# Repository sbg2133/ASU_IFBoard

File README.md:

# ASU_IFBoard
IF board schematics and PCB

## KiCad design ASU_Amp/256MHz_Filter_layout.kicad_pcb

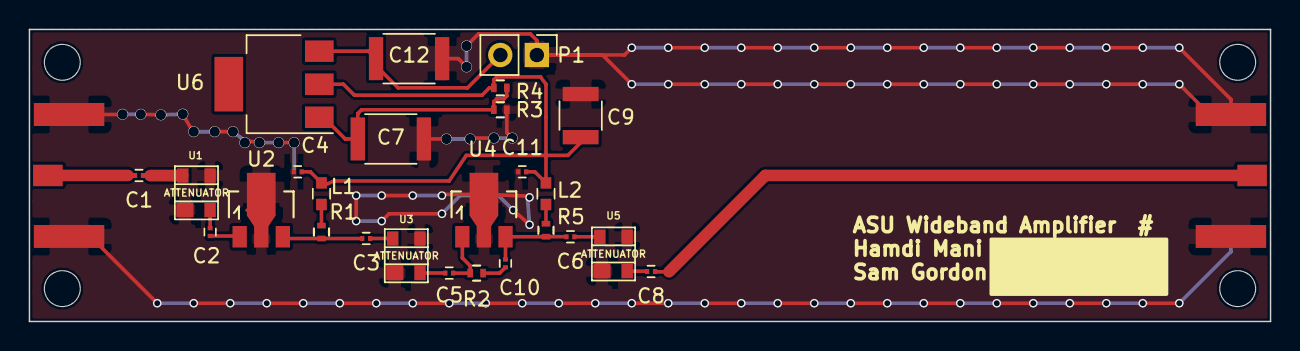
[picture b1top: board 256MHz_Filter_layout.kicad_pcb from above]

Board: 2 copper layers, 86.4 x 20.3 mm, 26 parts (0 on the bottom side), 17 nets.

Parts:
C1, C2, C3, C5, C6, C8, C10: 100pF; C_0201
C4, C11: 20pF; C_0201
C7, C12: 10uF; C_1812
C9: 100uF; C_1210
L1, L2: 1000nH; C_0603
P1: CONN_01X02; Pin_Header_Straight_1x02_Pitch2.54mm
R1, R2, R3, R4, R5: R; R_0402
U1, U3, U5: ATTENUATOR; sot143B
U2, U4: AMP; SOT89-3_Housing
U6: LM117; SOT-223

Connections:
/Vbias: C4.2, C9.2, C11.2, L1.2, L2.2, R3.1, U6.2
GND: C4.1, C7.1, C9.1, C11.1, C12.1, P1.1, R4.2, U1.1, U1.3, U2.2, U3.1, U3.3, U4.2, U5.1, U5.3
unnamed: C1.1, U1.4
unnamed: C2.1, U2.1
unnamed: C2.2, U1.2
unnamed: C3.1, U3.4
unnamed: C3.2, R1.2, U2.3
unnamed: C5.1, R2.2, U4.1
unnamed: C5.2, U3.2
unnamed: C6.1, U5.4
unnamed: C7.2, R3.2, R4.1, U6.1
unnamed: C8.2, U5.2
unnamed: C6.2, C10.1, R5.2, U4.3
unnamed: C10.2, R2.1
unnamed: C12.2, P1.2, U6.3
unnamed: L1.1, R1.1
unnamed: L2.1, R5.1

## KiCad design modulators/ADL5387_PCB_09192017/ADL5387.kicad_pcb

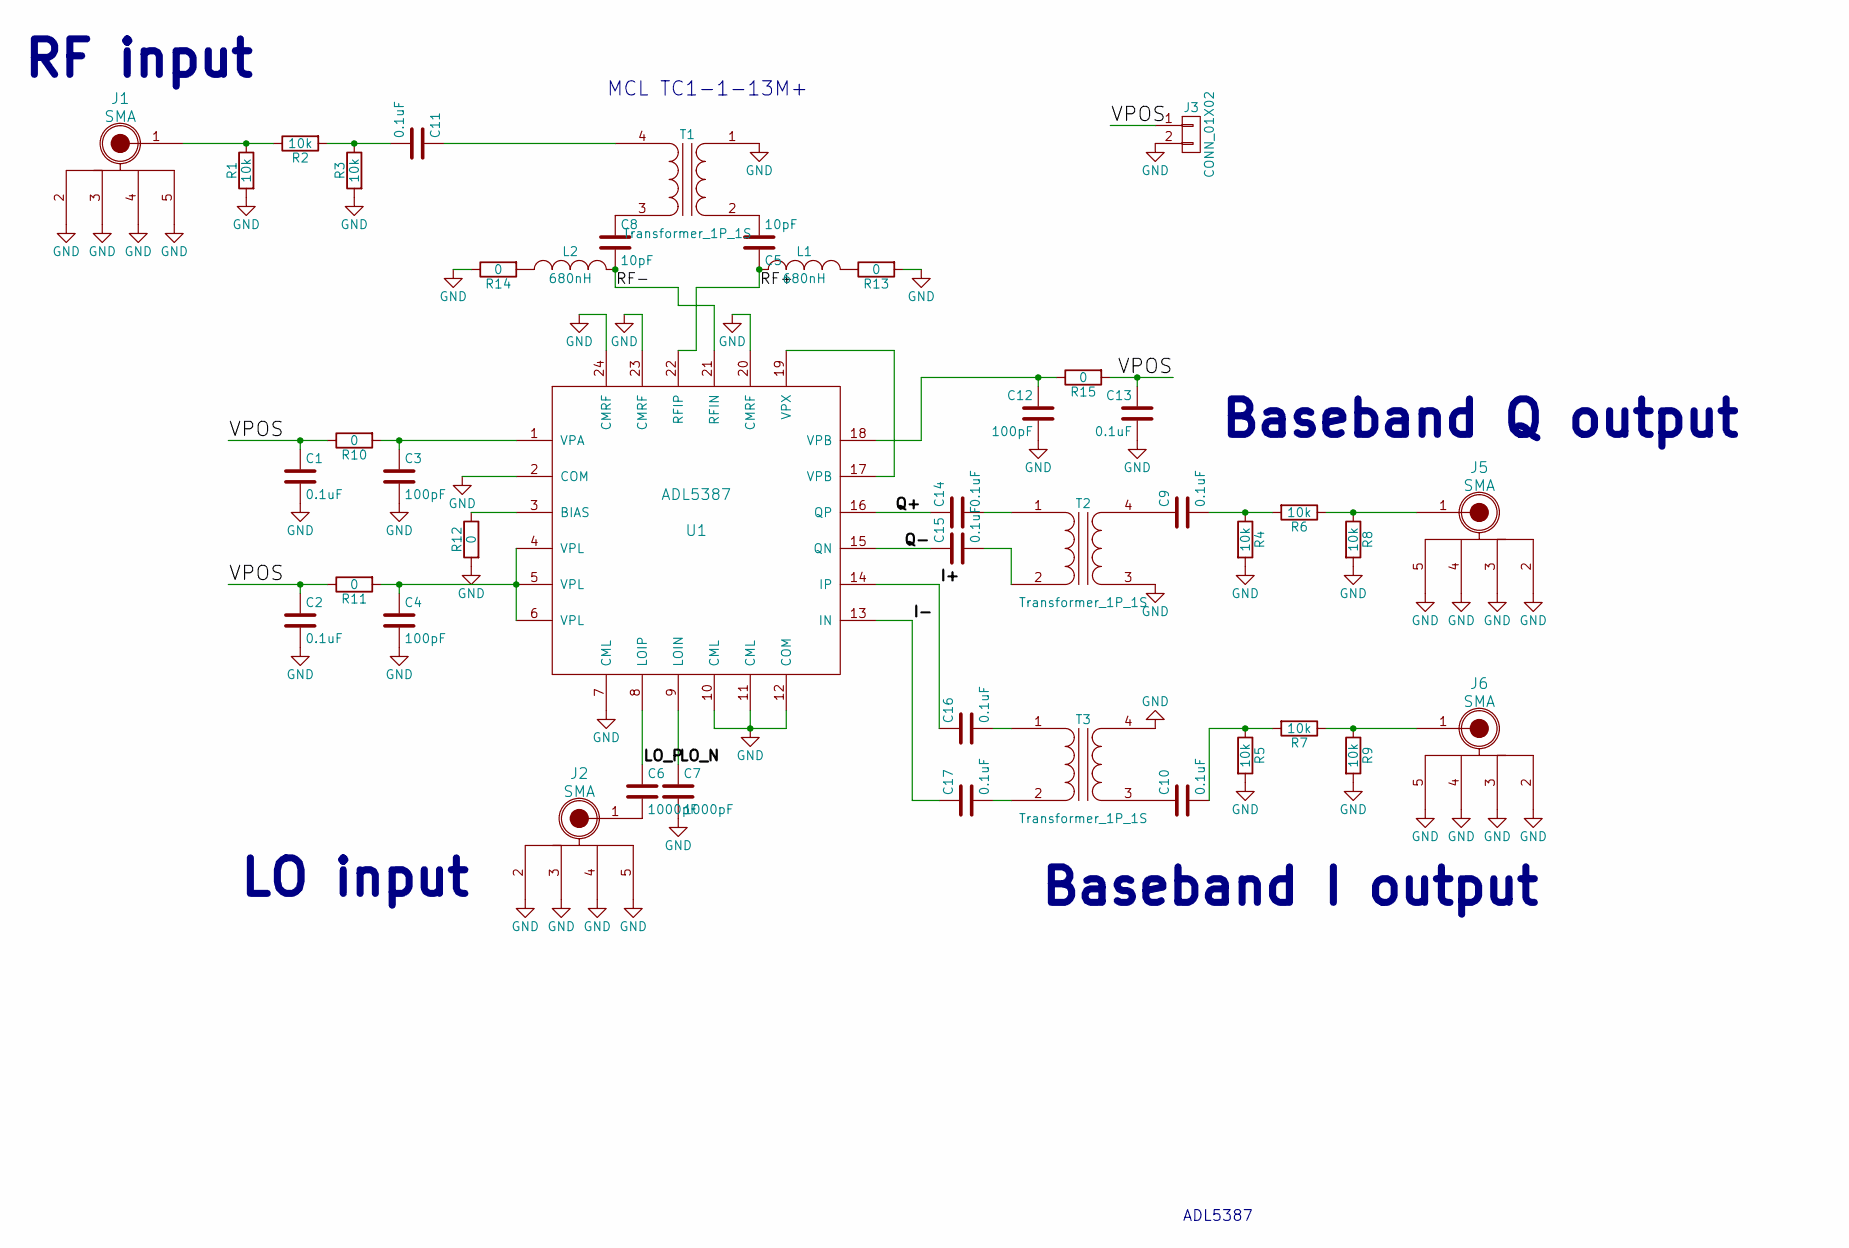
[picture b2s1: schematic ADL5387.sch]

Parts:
C1, C2, C9, C10, C11, C13, C14, C15, C16, C17: 0.1uF; SMD_0201
C3, C4, C12: 100pF; SMD_0201
C5, C8: 10pF; SMD_0201
C6, C7: 1000pF; SMD_0201
J1, J2, J5, J6: SMA; SMA_Edge_Amphenol
J3: CONN_01X02; Pin_Header_Straight_1x02_Pitch1.27mm
L1, L2: 680nH; L_0402
R1, R2, R3, R4, R5, R6, R7, R8, R9: 10k; SMD_0201
R10, R11, R12, R13, R14, R15: 0; SMD_0201
T1, T2, T3: Transformer_1P_1S; TC1-1-13M+
U1: ADL5387; QFN-24-1EP_4x4mm_Pitch0.5mm

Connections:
/I+: C16.1, U1.14 (IP)
/I-: C17.1, U1.13 (IN)
/LO_N: C7.1, U1.9 (LOIN)
/LO_P: C6.1, U1.8 (LOIP)
/Q+: C14.1, U1.16 (QP)
/Q-: C15.1, U1.15 (QN)
/RF+: C5.1, L1.2, U1.22 (RFIP)
/RF-: C8.2, L2.2, U1.21 (RFIN)
/VPOS: C1.1, C2.1, C13.1, J3.1, R10.1, R11.1, R15.2
GND: C1.2, C2.2, C3.2, C4.2, C7.2, C12.2, C13.2, J1.2, J1.3, J1.4, J1.5, J2.2, J2.3, J2.4, J2.5, J3.2, J5.2, J5.3, J5.4, J5.5, J6.2, J6.3, J6.4, J6.5, R1.2, R3.2, R4.2, R5.2, R8.2, R9.2, R12.2, R13.2, R14.1, T1.1 (AA), T2.3 (SA), T3.4 (SB), U1.2 (COM), U1.7 (CML), U1.10 (CML), U1.11 (CML), U1.12 (COM), U1.20 (CMRF), U1.23 (CMRF), U1.24 (CMRF), U1.25
unnamed: C3.1, R10.2, U1.1 (VPA)
unnamed: C4.1, R11.2, U1.4 (VPL), U1.5 (VPL), U1.6 (VPL)
unnamed: C5.2, T1.2 (AB)
unnamed: C6.2, J2.1
unnamed: C8.1, T1.3 (SA)
unnamed: C9.1, T2.4 (SB)
unnamed: C9.2, R4.1, R6.2
unnamed: C10.1, T3.3 (SA)
unnamed: C10.2, R5.1, R7.2
unnamed: C11.1, T1.4 (SB)
unnamed: C11.2, R2.2, R3.1
unnamed: C12.1, R15.1, U1.18 (VPB)
unnamed: C14.2, T2.1 (AA)
unnamed: C15.2, T2.2 (AB)
unnamed: C16.2, T3.1 (AA)
unnamed: C17.2, T3.2 (AB)
unnamed: J1.1, R1.1, R2.1
unnamed: J5.1, R6.1, R8.1
unnamed: J6.1, R7.1, R9.1
unnamed: L1.1, R13.1
unnamed: L2.1, R14.2
unnamed: R12.1, U1.3 (BIAS)
unnamed: U1.17 (VPB), U1.19 (VPX)

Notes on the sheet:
LO input
Baseband I output
Baseband Q output
ADL5387
MCL TC1-1-13M+
RF input

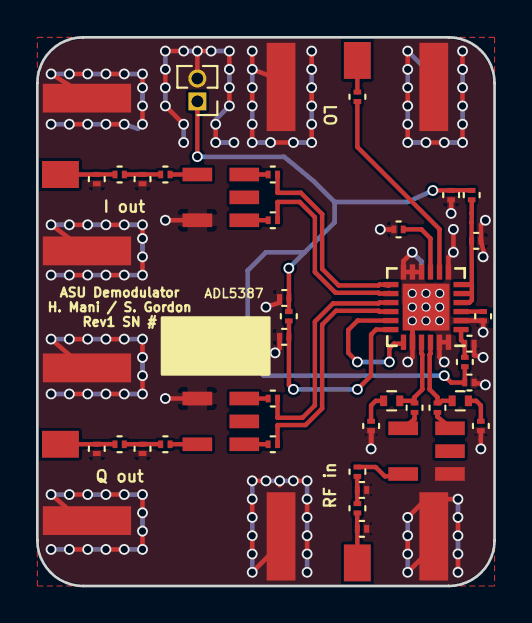
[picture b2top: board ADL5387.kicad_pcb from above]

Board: 2 copper layers, 25.4 x 30.5 mm, 43 parts (0 on the bottom side), 33 nets.

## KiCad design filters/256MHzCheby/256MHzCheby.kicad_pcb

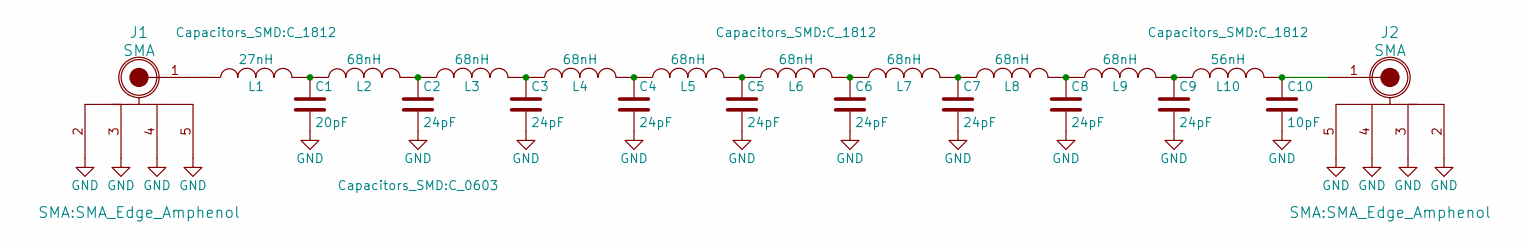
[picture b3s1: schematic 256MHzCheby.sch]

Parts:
C1: 20pF; C_0603
C2, C3, C4, C5, C6, C7, C8, C9: 24pF; C_0603
C10: 10pF; C_0603
J1, J2: SMA; SMA_Edge_Amphenol
L1: 27nH; C_1812
L2, L3, L4, L5, L6, L7, L8, L9: 68nH; C_1812
L10: 56nH; C_1812

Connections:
GND: C1.2, C2.2, C3.2, C4.2, C5.2, C6.2, C7.2, C8.2, C9.2, C10.2, J1.2, J1.3, J1.4, J1.5, J2.2, J2.3, J2.4, J2.5
unnamed: C1.1, L1.2, L2.1
unnamed: C2.1, L2.2, L3.1
unnamed: C3.1, L3.2, L4.1
unnamed: C4.1, L4.2, L5.1
unnamed: C5.1, L5.2, L6.1
unnamed: C6.1, L6.2, L7.1
unnamed: C7.1, L7.2, L8.1
unnamed: C8.1, L8.2, L9.1
unnamed: C9.1, L9.2, L10.1
unnamed: C10.1, J2.1, L10.2
unnamed: J1.1, L1.1

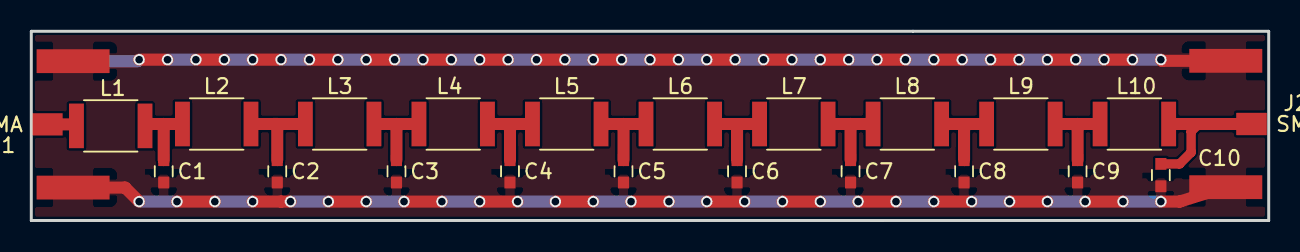
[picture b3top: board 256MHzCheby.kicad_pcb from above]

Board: 2 copper layers, 83.1 x 12.7 mm, 22 parts (0 on the bottom side), 12 nets.

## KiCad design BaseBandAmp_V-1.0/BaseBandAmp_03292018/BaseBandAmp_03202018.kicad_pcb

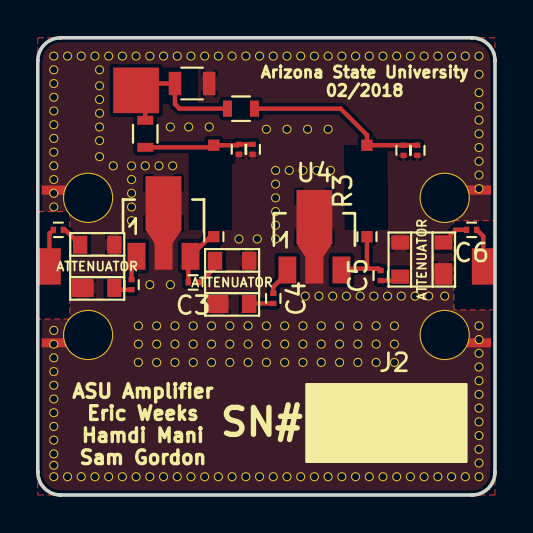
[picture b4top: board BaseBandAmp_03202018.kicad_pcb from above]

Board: 2 copper layers, 25.4 x 25.4 mm, 15 parts (0 on the bottom side), 10 nets.

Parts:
C3, C4, C5, C6, C8, C8#2, C8#3, C8#4: 100pF; C_0201
J2: SMA_Edge_Amphenol
R3, R3#2: 1.45H; Inductor_BaseBandAmp
U1, U3, U5: ATTENUATOR; sot143B
U4: AMP; SOT89-3_Housing

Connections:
GND: C8.1, C8#2.1, C8#3.1, C8#4.1, J2.2, J2.3, J2.4, J2.5, U1.1, U1.3, U3.1, U3.3, U4.2, U5.1, U5.3
unnamed: C3.1, U3.4
unnamed: C3.2, R3#2.1
unnamed: C4.1, U4.1
unnamed: C4.2, U3.2
unnamed: C5.1, U5.4
unnamed: C5.2, R3.1, U4.3
unnamed: C6.1, J2.1
unnamed: C6.2, U5.2
unnamed: C8.2, C8#2.2, C8#3.2, C8#4.2, R3.2, R3#2.2

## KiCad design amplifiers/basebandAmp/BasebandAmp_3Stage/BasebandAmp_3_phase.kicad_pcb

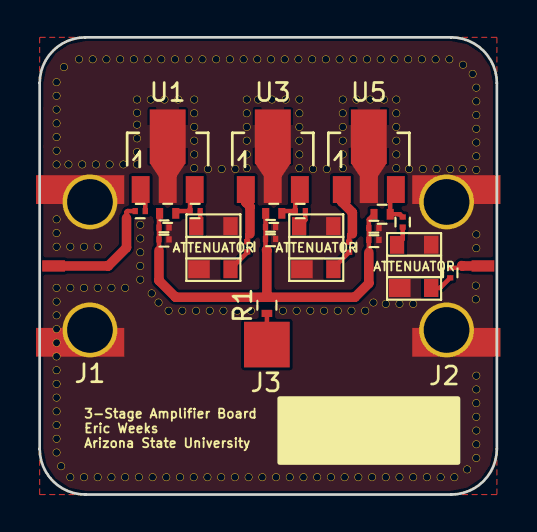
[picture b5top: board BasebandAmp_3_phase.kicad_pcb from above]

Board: 2 copper layers, 25.4 x 25.4 mm, 26 parts (0 on the bottom side), 17 nets.

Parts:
C1, C2, C3, C4, C5, C6, C7, C8, C9, C10, C11, C12, C13: 100pF; C_0201
J1, J2: SMA; SMA_Edge_Amphenol
J3: 5V_DC; SolderWirePad_single_SMD_5x10mm
R1, R2, R3, R4: 10ohm; R_0402
U1, U3, U5: AMP; SOT89-3_Housing
U2, U4, U6: ATTENUATOR; sot143B

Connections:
GND: C8.1, C9.1, C10.1, C11.1, C12.1, C13.1, J1.2, J1.3, J1.4, J1.5, J2.2, J2.3, J2.4, J2.5, U1.2, U2.1, U2.3, U3.2, U4.1, U4.3, U5.2, U6.1, U6.3
unnamed: C1.1, U1.1
unnamed: C1.2, J1.1
unnamed: C2.1, U2.4
unnamed: C2.2, R2.1, U1.3
unnamed: C3.1, U3.1
unnamed: C3.2, U2.2
unnamed: C4.1, U4.4
unnamed: C4.2, R3.1, U3.3
unnamed: C5.1, U5.1
unnamed: C5.2, U4.2
unnamed: C6.1, U6.4
unnamed: C6.2, R4.1, U5.3
unnamed: C7.1, J2.1
unnamed: C7.2, U6.2
unnamed: C8.2, C9.2, C10.2, C11.2, C12.2, C13.2, R1.2, R2.2, R3.2, R4.2
unnamed: J3.1, R1.1

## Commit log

2017-09-27 Adding draft files
2018-01-25 Adding latest baseband amp design
2018-02-01 Adding footprints library
